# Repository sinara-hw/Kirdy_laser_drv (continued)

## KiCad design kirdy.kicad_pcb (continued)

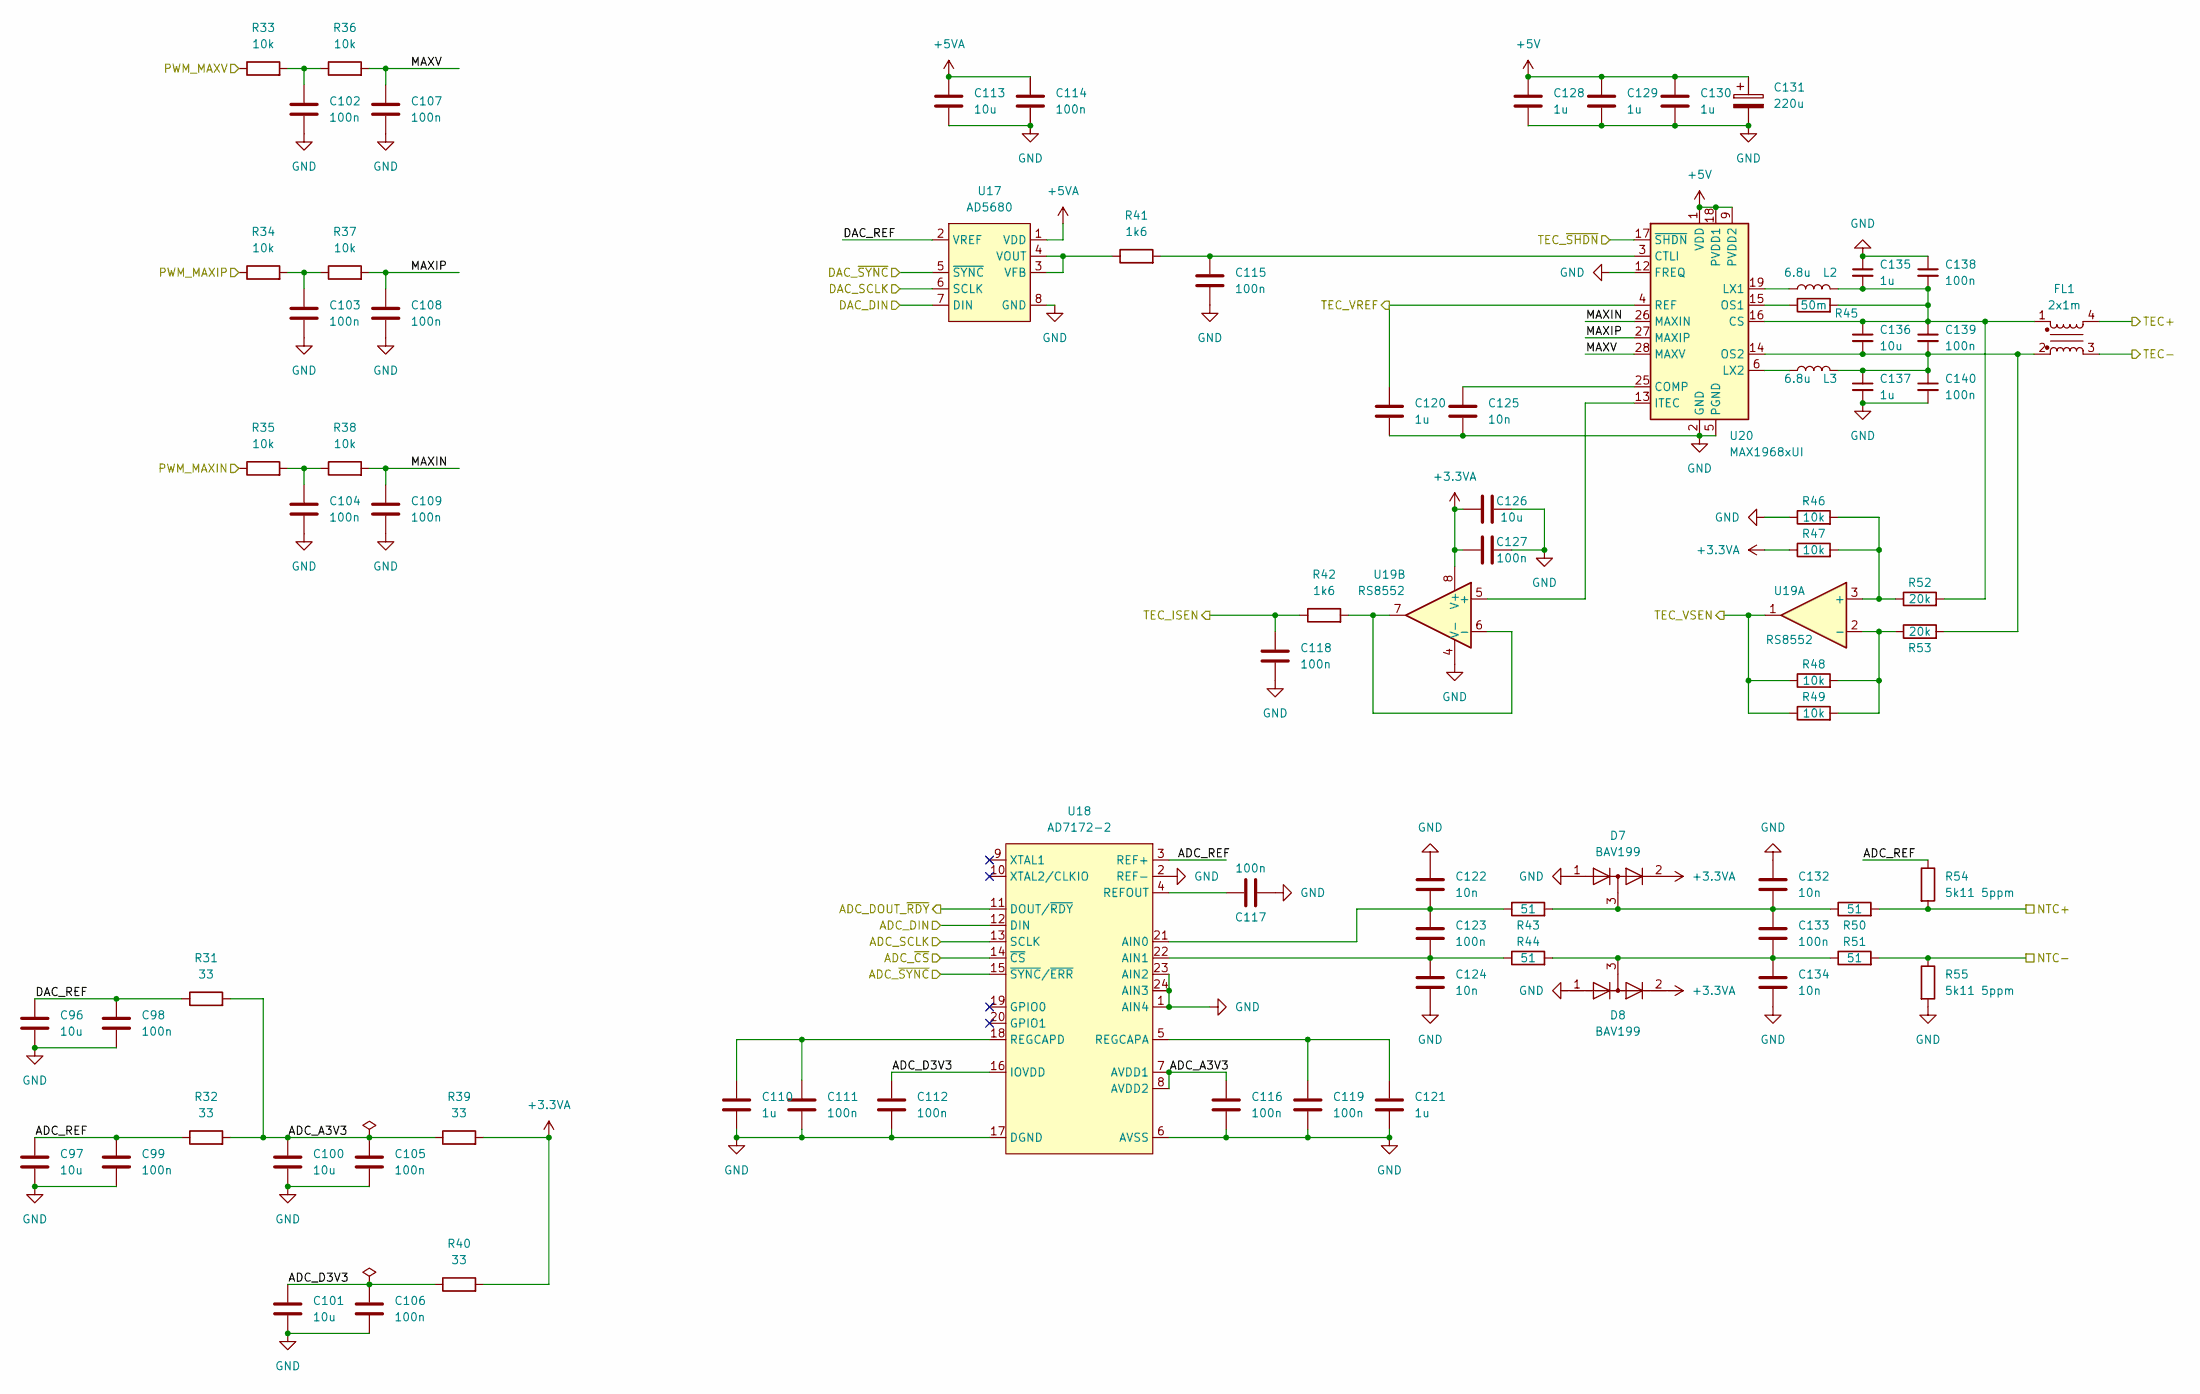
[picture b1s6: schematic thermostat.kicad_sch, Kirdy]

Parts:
C96, C97, C100, C101, C113, C126, C136: 10u; C_0805_2012Metric; MFR_PN CL21B106KOQNNNG
C98, C99, C102, C103, C104, C105, C106, C107, C108, C109, C111, C112, C114, C115, C116, C117, C118, C119, C123, C127, C133, C138, C139, C140: 100n; C_0603_1608Metric; MFR_PN CL10B104KB8NNWC
C110, C120, C121, C128, C129, C130, C135, C137: 1u; C_0603_1608Metric; MFR_PN CL10B105KA8NNNC
C122, C124, C125, C132, C134: 10n; C_0603_1608Metric; MFR_PN 0603B103K500CT
C131: 220u; CP_EIA-7343-15_Kemet-W; MFR_PN T491D227K016AT
D7, D8: BAV199; SOT-23; MFR_PN BAV199W-7
FL1: 2x1m; L_CommonModeChoke_Wuerth_WE-SL5; MFR_PN 744273501
L2, L3: 6.8u; L_Wuerth_MAPI-4030; MFR_PN 74438357068
R31, R32, R39, R40: 33; R_0603_1608Metric; MFR_PN RC0603FR-0733RL
R33, R34, R35, R36, R37, R38, R46, R47, R48, R49: 10k; R_0603_1608Metric; MFR_PN RNCP0603FTD10K0
R41, R42: 1k6; R_0603_1608Metric; MFR_PN RT0603FRE071K6L
R43, R44, R50, R51: 51; R_0603_1608Metric; MFR_PN ESR03EZPF51R0
R45: 50m; R_2010_5025Metric; MFR_PN WSL2010R5000FEA18
R52, R53: 20k; R_0603_1608Metric; MFR_PN RMCF0603FT20K0
R54, R55: 5k11 5ppm; R_0603_1608Metric; MFR_PN RN73H1JTTD5111A05
U17: AD5680; SOT-23-8; MFR_PN AD5680BRJZ
U18: AD7172-2; TSSOP-24_4.4x7.8mm_P0.65mm; MFR_PN AD7172-2BRUZ
U19: RS8552; SOIC-8_3.9x4.9mm_P1.27mm; MFR_PN RS8552XK
U20: MAX1968xUI; HTSSOP-28-1EP_4.4x9.7mm_P0.65mm_EP2.85x5.4mm; MFR_PN MAX1968EUI+

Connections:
+3.3VA: C126.1, C127.1, D7.2 (A), D8.2 (A), R39.2, R40.2, R47.1, U19.8 (V+); also elsewhere on the board
+5V: C128.1, C129.1, C130.1, C131.1, U20.1 (VDD), U20.9 (PVDD2), U20.11 (PVDD2), U20.18 (PVDD1), U20.20 (PVDD1); also elsewhere on the board
+5VA: C113.1, C114.1, U17.1 (VDD); also elsewhere on the board
/MCU/PWM_MAXIN: R35.1; also elsewhere on the board
/MCU/PWM_MAXIP: R34.1; also elsewhere on the board
/MCU/PWM_MAXV: R33.1; also elsewhere on the board
/MCU/TADC_CLK: U18.13 (SCLK); also elsewhere on the board
/MCU/TADC_CS: U18.12 (DIN); also elsewhere on the board
/MCU/TADC_MISO: U18.14 (~CS); also elsewhere on the board
/MCU/TADC_MOSI: U18.11 (DOUT/~RDY); also elsewhere on the board
/MCU/TADC_SYNC: U18.15 (~SYNC/~ERR); also elsewhere on the board
/MCU/TDAC_CLK: U17.6 (SCLK); also elsewhere on the board
/MCU/TDAC_MOSI: U17.7 (DIN); also elsewhere on the board
/MCU/TDAC_SYNC: U17.5 (~SYNC); also elsewhere on the board
/MCU/TEC_ISEN: C118.1, R42.1; also elsewhere on the board
/MCU/TEC_SHDN: U20.17 (~SHDN); also elsewhere on the board
/MCU/TEC_VREF: C120.1, U20.4 (REF); also elsewhere on the board
/MCU/TEC_VSEN: R48.1, R49.1, U19.1; also elsewhere on the board
/thermostat/ADC_A3V3: C100.1, C105.1, C116.1, R31.2, R32.2, R39.1, U18.7 (AVDD1), U18.8 (AVDD2)
/thermostat/ADC_D3V3: C101.1, C106.1, C112.1, R40.1, U18.16 (IOVDD)
/thermostat/ADC_REF: C97.1, C99.1, R32.1, R54.1, U18.3 (REF+)
/thermostat/DAC_REF: C96.1, C98.1, R31.1, U17.2 (VREF)
/thermostat/MAXIN: C109.1, R38.2, U20.26 (MAXIN)
/thermostat/MAXIP: C108.1, R37.2, U20.27 (MAXIP)
/thermostat/MAXV: C107.1, R36.2, U20.28 (MAXV)
/thermostat/NTC+: R50.2, R54.2; also elsewhere on the board
/thermostat/NTC-: R51.2, R55.1; also elsewhere on the board
/thermostat/TEC+: FL1.4; also elsewhere on the board
/thermostat/TEC-: FL1.3; also elsewhere on the board
GND: C96.2, C97.2, C98.2, C99.2, C100.2, C101.2, C102.2, C103.2, C104.2, C105.2, C106.2, C107.2, C108.2, C109.2, C110.2, C111.2, C112.2, C113.2, C114.2, C115.2, C116.2, C117.2, C118.2, C119.2, C120.2, C121.2, C122.1, C124.2, C125.2, C126.2, C127.2, C128.2, C129.2, C130.2, C131.2, C132.1, C134.2, C135.1, C137.2, C138.1, C140.2, D7.1 (K), D8.1 (K), R46.1, R55.2, U17.8 (GND), U18.1 (AIN4), U18.2 (REF-), U18.6 (AVSS), U18.17 (DGND), U18.23 (AIN2), U18.24 (AIN3), U19.4 (V-), U20.2 (GND), U20.5 (PGND), U20.7 (PGND), U20.12 (FREQ), U20.22 (PGND), U20.24 (PGND), U20.29 (GND); also elsewhere on the board
unnamed: C102.1, R33.2, R36.1
unnamed: C103.1, R34.2, R37.1
unnamed: C104.1, R35.2, R38.1
unnamed: C110.1, C111.1, U18.18 (REGCAPD)
unnamed: C115.1, R41.2, U20.3 (CTLI)
unnamed: C117.1, U18.4 (REFOUT)
unnamed: C119.1, C121.1, U18.5 (REGCAPA)
unnamed: C122.2, C123.1, R43.1, U18.21 (AIN0)
unnamed: C123.2, C124.1, R44.1, U18.22 (AIN1)
unnamed: C125.1, U20.25 (COMP)
unnamed: C132.2, C133.1, D7.3 (K), R43.2, R50.1
unnamed: C133.2, C134.1, D8.3 (K), R44.2, R51.1
unnamed: C135.2, C136.1, C138.2, C139.1, FL1.1, L2.2, R45.2, R52.2, U20.16 (CS)
unnamed: C136.2, C137.1, C139.2, C140.1, FL1.2, L3.2, R53.2, U20.14 (OS2)
unnamed: L2.1, U20.19 (LX1), U20.21 (LX1), U20.23 (LX1)
unnamed: L3.1, U20.6 (LX2), U20.8 (LX2), U20.10 (LX2)
unnamed: R41.1, U17.3 (VFB), U17.4 (VOUT)
unnamed: R42.2, U19.6 (-), U19.7
unnamed: R45.1, U20.15 (OS1)
unnamed: R46.2, R47.2, R52.1, U19.3 (+)
unnamed: R48.2, R49.2, R53.1, U19.2 (-)
unnamed: U19.5 (+), U20.13 (ITEC)

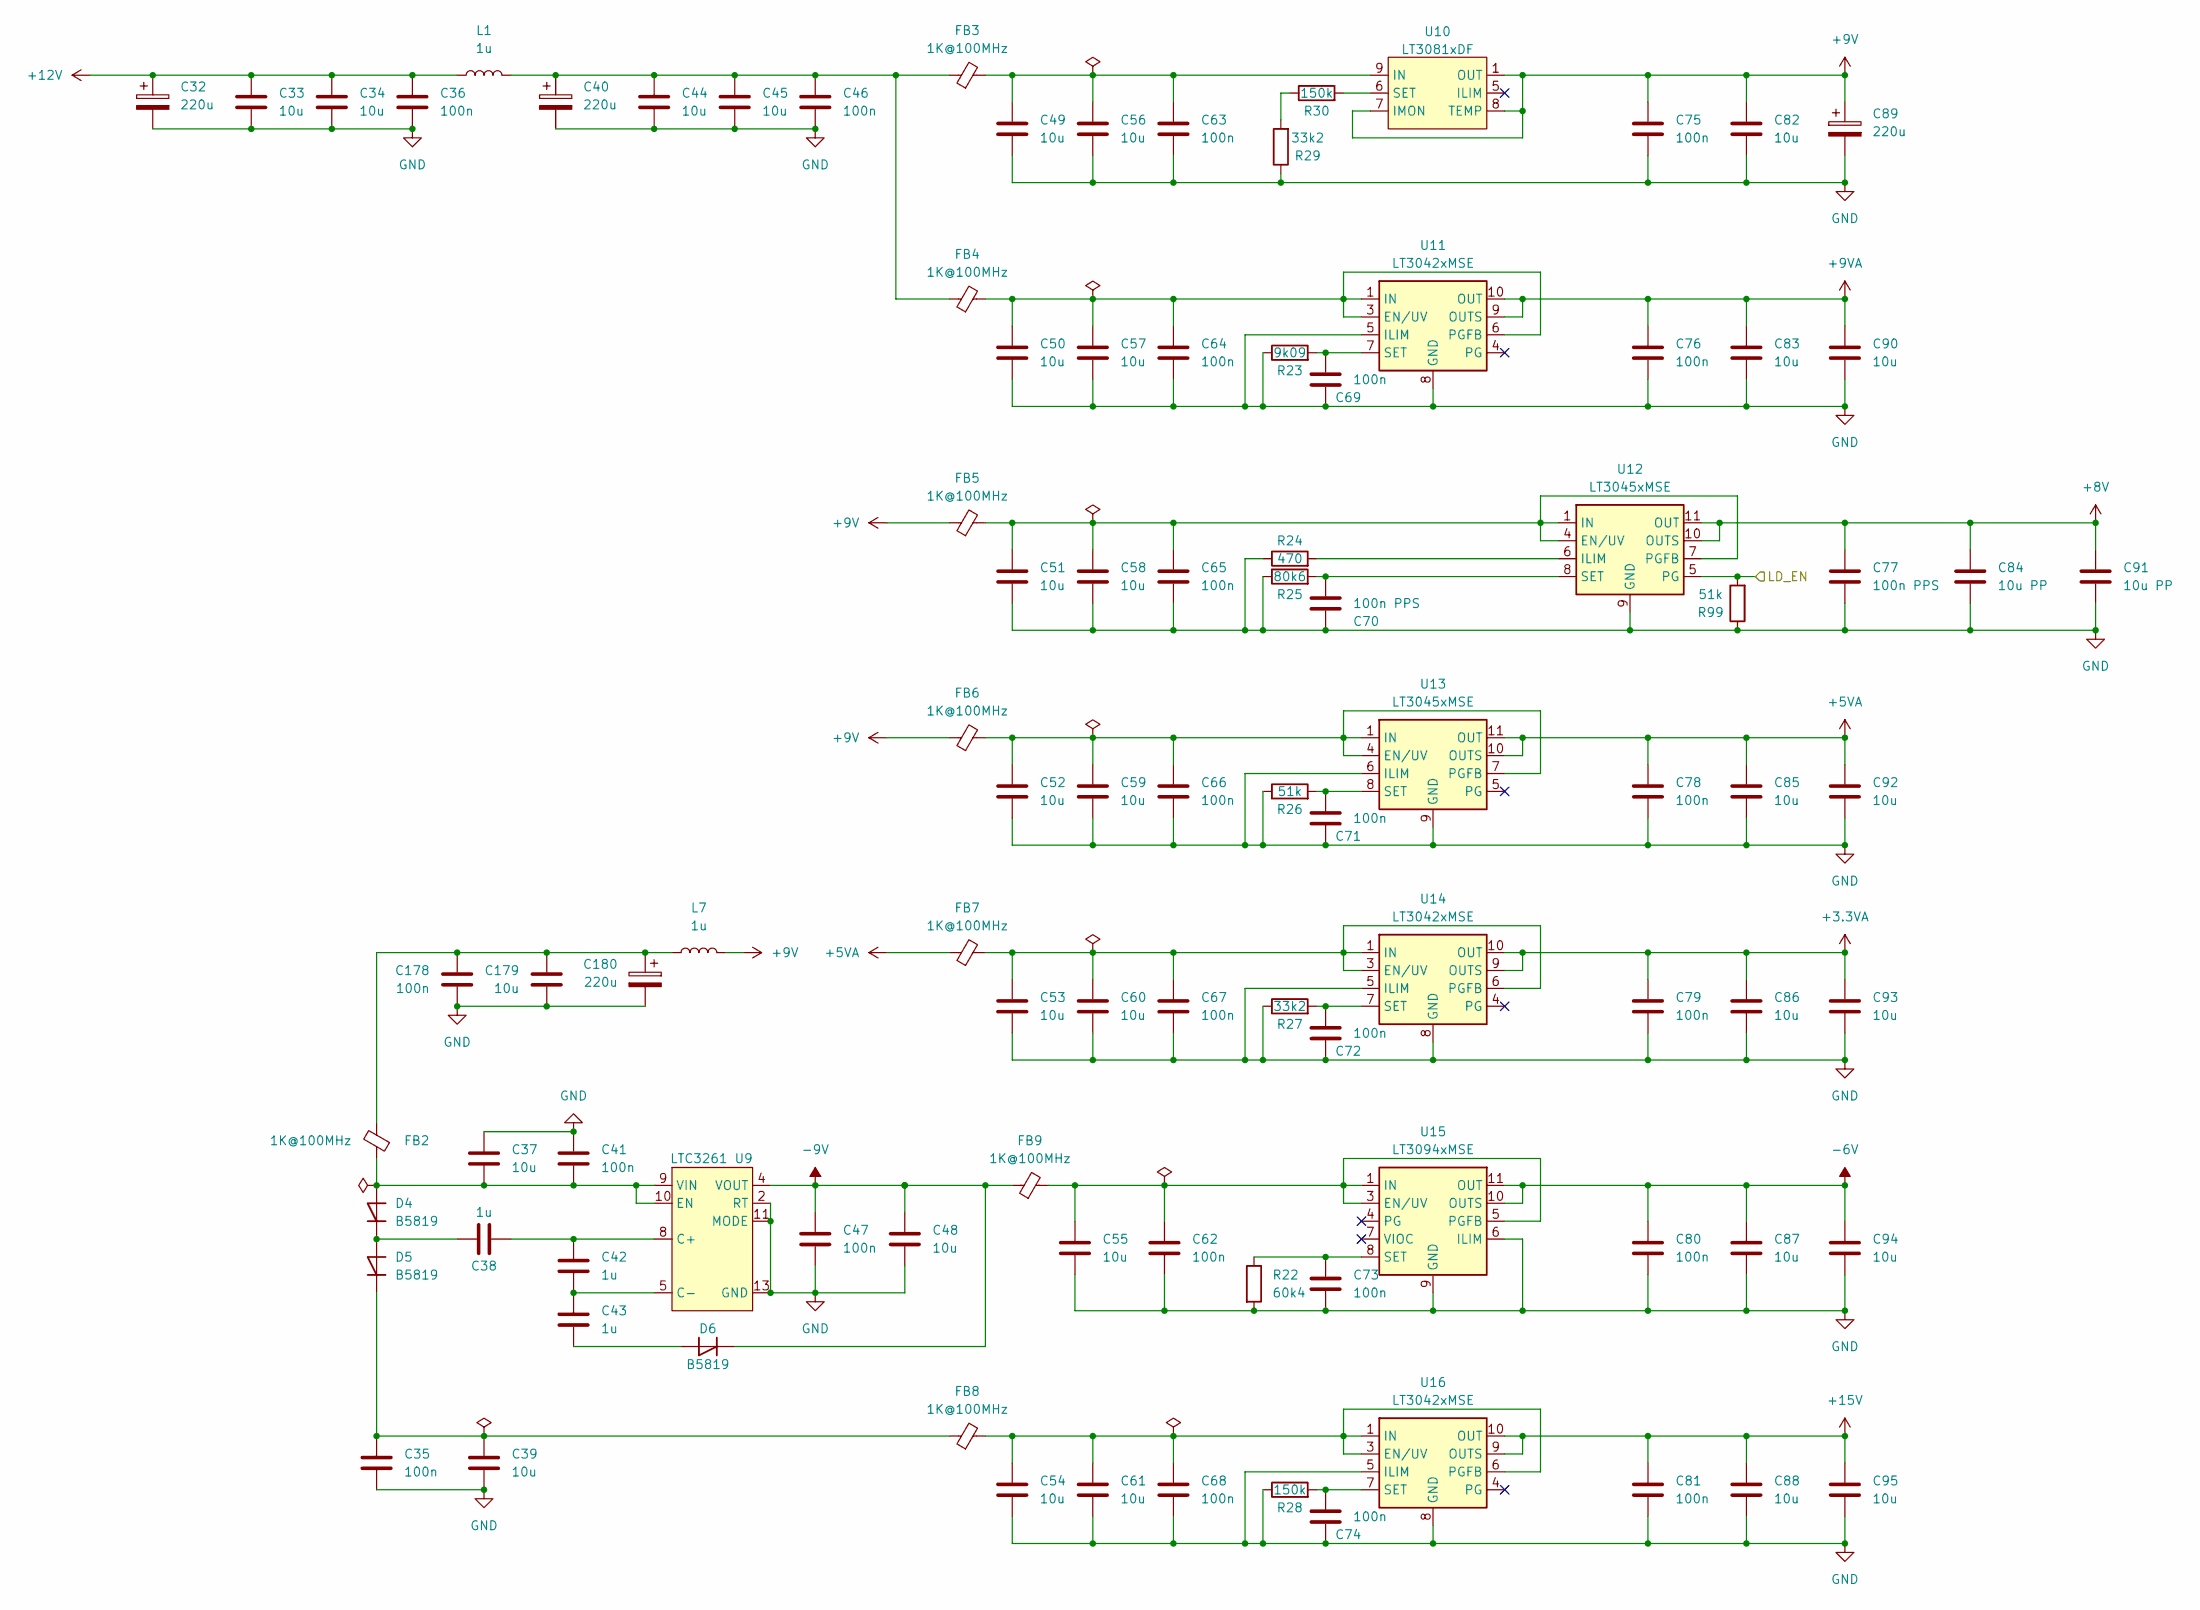
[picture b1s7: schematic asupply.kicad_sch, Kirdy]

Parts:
C32, C40, C89, C180: 220u; CP_EIA-7343-15_Kemet-W; MFR_PN T491D227K016AT
C33, C34, C37, C39, C44, C45, C48, C49, C50, C51, C52, C53, C54, C55, C56, C57, C58, C59, C60, C61, C82, C83, C85, C86, C87, C88, C90, C92, C93, C94, C95, C179: 10u; C_0805_2012Metric; MFR_PN CL21B106KOQNNNG
C35, C36, C41, C46, C47, C62, C63, C64, C65, C66, C67, C68, C69, C71, C72, C73, C74, C75, C76, C78, C79, C80, C81, C178: 100n; C_0603_1608Metric; MFR_PN CL10B104KB8NNWC
C38, C42, C43: 1u; C_0603_1608Metric; MFR_PN CL10B105KA8NNNC
C70, C77: 100n PPS; C_1210_3225Metric; MFR_PN ECH-U1C104JX5
C84, C91: 10u PP; C_1812_4532Metric; MFR_PN 16MU106MC44532
D4, D5, D6: B5819; D_SOD-323; MFR_PN B5819WS-TP
FB2, FB3, FB4, FB5, FB6, FB7, FB8, FB9: 1K@100MHz; L_1210_3225Metric; MFR_PN FBMH3225HM102NT
L1, L7: 1u; L_1008_2520Metric; MFR_PN DFE252012F-1R0M=P2
R22: 60k4; R_0603_1608Metric; MFR_PN RT0603FRE0760K4L
R23: 9k09; R_0603_1608Metric; MFR_PN CR0603-FX-9091ELF
R24: 470; R_0603_1608Metric; MFR_PN WR06X4700FTL
R25: 80k6; R_0603_1608Metric; MFR_PN RC0603FR-0780K6L
R26, R99: 51k; R_0603_1608Metric; MFR_PN RMCF0603FT51K0
R27, R29: 33k2; R_0603_1608Metric; MFR_PN CR0603-FX-3322ELF
R28, R30: 150k; R_0603_1608Metric; MFR_PN CRGCQ0603F150K
U9: LTC3261; MSOP-12-1EP_3x4mm_P0.65mm_EP1.65x2.85mm; MFR_PN LTC3261IMSE#TRPBF
U10: LT3081xDF; DFN-12-1EP_4x4mm_P0.5mm_EP2.66x3.38mm; MFR_PN LT3081EDF
U11, U14, U16: LT3042xMSE; MSOP-10-1EP_3x3mm_P0.5mm_EP1.68x1.88mm; MFR_PN LT3042IMSE#PBF
U12, U13: LT3045xMSE; MSOP-12-1EP_3x4mm_P0.65mm_EP1.65x2.85mm; MFR_PN LT3045EMSE-1#PBF
U15: LT3094xMSE; MSOP-12-1EP_3x4mm_P0.65mm_EP1.65x2.85mm; MFR_PN LT3094IMSE#PBF

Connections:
+3.3VA: C79.1, C86.1, C93.1, U14.9 (OUTS), U14.10 (OUT); also elsewhere on the board
+5VA: C78.1, C85.1, C92.1, FB7.1, U13.10 (OUTS), U13.11 (OUT), U13.12 (OUT); also elsewhere on the board
+8V: C77.1, C84.1, C91.1, U12.10 (OUTS), U12.11 (OUT), U12.12 (OUT); also elsewhere on the board
+9V: C75.1, C82.1, C89.1, FB5.1, FB6.1, L7.1, U10.1 (OUT), U10.2 (OUT), U10.3 (OUT), U10.4 (OUT), U10.7 (IMON), U10.8 (TEMP), U10.13 (OUT)
+9VA: C76.1, C83.1, C90.1, U11.9 (OUTS), U11.10 (OUT); also elsewhere on the board
+12V: C32.1, C33.1, C34.1, C36.1, L1.1; also elsewhere on the board
+15V: C81.1, C88.1, C95.1, U16.9 (OUTS), U16.10 (OUT); also elsewhere on the board
-6V: C80.1, C87.1, C94.1, U15.10 (OUTS), U15.11 (OUT), U15.12 (OUT); also elsewhere on the board
-9V: C47.1, C48.1, D6.1 (K), FB9.1, U9.4 (VOUT)
/MCU/LD_EN: R99.2, U12.5 (PG); also elsewhere on the board
GND: C32.2, C33.2, C34.2, C35.2, C36.2, C37.1, C39.2, C40.2, C41.1, C44.2, C45.2, C46.2, C47.2, C48.2, C49.2, C50.2, C51.2, C52.2, C53.2, C54.2, C55.2, C56.2, C57.2, C58.2, C59.2, C60.2, C61.2, C62.2, C63.2, C64.2, C65.2, C66.2, C67.2, C68.2, C69.2, C70.2, C71.2, C72.2, C73.2, C74.2, C75.2, C76.2, C77.2, C78.2, C79.2, C80.2, C81.2, C82.2, C83.2, C84.2, C85.2, C86.2, C87.2, C88.2, C89.2, C90.2, C91.2, C92.2, C93.2, C94.2, C95.2, C178.2, C179.2, C180.2, R22.2, R23.1, R24.1, R25.1, R26.1, R27.1, R28.1, R29.1, R99.1, U9.2 (RT), U9.11 (MODE), U9.13 (GND), U11.5 (ILIM), U11.8 (GND), U11.11 (GND), U12.9 (GND), U12.13 (GND), U13.6 (ILIM), U13.9 (GND), U13.13 (GND), U14.5 (ILIM), U14.8 (GND), U14.11 (GND), U15.6 (ILIM), U15.9 (GND), U16.5 (ILIM), U16.8 (GND), U16.11 (GND); also elsewhere on the board
IN: C49.1, C56.1, C63.1, FB3.2, U10.9 (IN), U10.10 (IN), U10.11 (IN), U10.12 (IN)
unnamed: C35.1, C39.1, D5.1 (K), FB8.1
unnamed: C37.2, C41.2, D4.2 (A), FB2.1, U9.9 (VIN), U9.10 (EN)
unnamed: C38.1, D4.1 (K), D5.2 (A)
unnamed: C38.2, C42.1, U9.8 (C+)
unnamed: C40.1, C44.1, C45.1, C46.1, FB3.1, FB4.1, L1.2
unnamed: C42.2, C43.1, U9.5 (C-)
unnamed: C43.2, D6.2 (A)
unnamed: C50.1, C57.1, C64.1, FB4.2, U11.1 (IN), U11.2 (IN), U11.3 (EN/UV), U11.6 (PGFB)
unnamed: C51.1, C58.1, C65.1, FB5.2, U12.1 (IN), U12.2 (IN), U12.3 (IN), U12.4 (EN/UV), U12.7 (PGFB)
unnamed: C52.1, C59.1, C66.1, FB6.2, U13.1 (IN), U13.2 (IN), U13.3 (IN), U13.4 (EN/UV), U13.7 (PGFB)
unnamed: C53.1, C60.1, C67.1, FB7.2, U14.1 (IN), U14.2 (IN), U14.3 (EN/UV), U14.6 (PGFB)
unnamed: C54.1, C61.1, C68.1, FB8.2, U16.1 (IN), U16.2 (IN), U16.3 (EN/UV), U16.6 (PGFB)
unnamed: C55.1, C62.1, FB9.2, U15.1 (IN), U15.2 (IN), U15.3 (EN/UV), U15.5 (PGFB), U15.13 (IN)
unnamed: C69.1, R23.2, U11.7 (SET)
unnamed: C70.1, R25.2, U12.8 (SET)
unnamed: C71.1, R26.2, U13.8 (SET)
unnamed: C72.1, R27.2, U14.7 (SET)
unnamed: C73.1, R22.1, U15.8 (SET)
unnamed: C74.1, R28.2, U16.7 (SET)
unnamed: C178.1, C179.1, C180.1, FB2.2, L7.2
unnamed: R24.2, U12.6 (ILIM)
unnamed: R29.2, R30.1
unnamed: R30.2, U10.6 (SET)

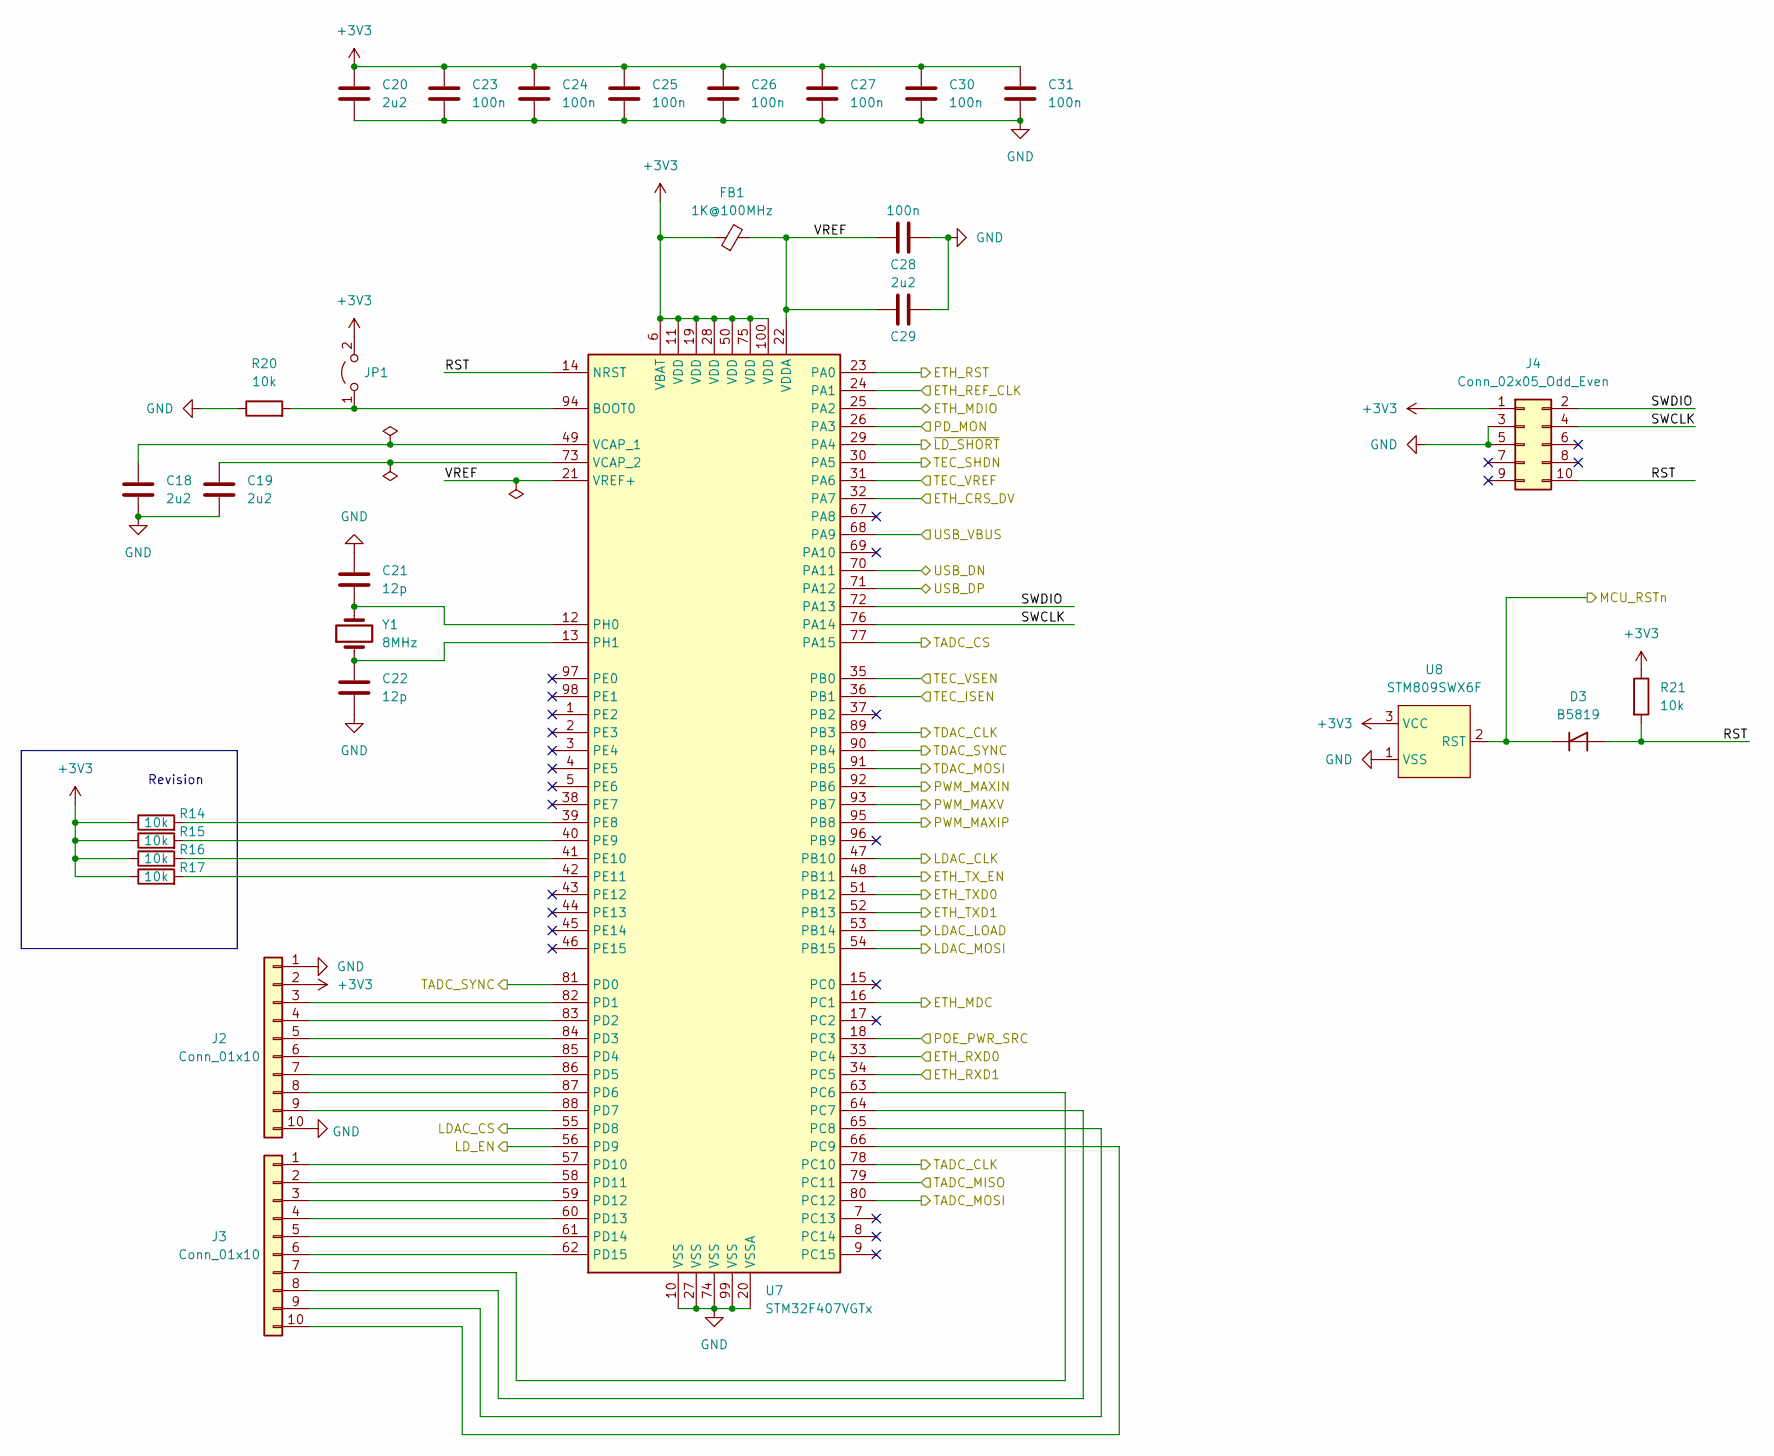
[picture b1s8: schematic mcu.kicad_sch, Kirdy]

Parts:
C18, C19, C20, C29: 2u2; C_0603_1608Metric; MFR_PN CL10B225KP8NNNC
C21, C22: 12p; C_0603_1608Metric; MFR_PN 0603N120J500CT
C23, C24, C25, C26, C27, C28, C30, C31: 100n; C_0603_1608Metric; MFR_PN CL10B104KB8NNWC
D3: B5819; D_SOD-323; MFR_PN B5819WS-TP
FB1: 1K@100MHz; L_1210_3225Metric; MFR_PN FBMH3225HM102NT
J2, J3: Conn_01x10; PinHeader_1x10_P2.54mm_Vertical
J4: Conn_02x05_Odd_Even; PinHeader_2x05_P1.27mm_Vertical_SMD; MFR_PN M50-3600542
JP1: DNP; PinHeader_1x02_P2.54mm_Vertical
R14, R15, R16, R17, R20, R21: 10k; R_0603_1608Metric; MFR_PN RNCP0603FTD10K0
U7: STM32F407VGTx; LQFP-100_14x14mm_P0.5mm; MFR_PN STM32F407VGT6
U8: STM809SWX6F; SOT-23; MFR_PN STM809SWX6F
Y1: 8MHz; Crystal_SMD_5032-2Pin_5.0x3.2mm; MFR_PN ECS-80-12-30Q-DS-TR

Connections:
+3V3: C20.1, C23.1, C24.1, C25.1, C26.1, C27.1, C30.1, C31.1, FB1.1, J2.2, J4.1, JP1.2 (B), R14.1, R15.1, R16.1, R17.1, R21.1, U7.6 (VBAT), U7.11 (VDD), U7.19 (VDD), U7.28 (VDD), U7.50 (VDD), U7.75 (VDD), U7.100 (VDD), U8.3 (VCC); also elsewhere on the board
/Ehternet/PHY_NRST: U7.23 (PA0); also elsewhere on the board
/Ehternet/RMII_CRS_DV: U7.32 (PA7); also elsewhere on the board
/Ehternet/RMII_MDC: U7.16 (PC1); also elsewhere on the board
/Ehternet/RMII_MDIO: U7.25 (PA2); also elsewhere on the board
/Ehternet/RMII_REF_CLK: U7.24 (PA1); also elsewhere on the board
/Ehternet/RMII_RXD0: U7.33 (PC4); also elsewhere on the board
/Ehternet/RMII_RXD1: U7.34 (PC5); also elsewhere on the board
/Ehternet/RMII_TXD0: U7.51 (PB12); also elsewhere on the board
/Ehternet/RMII_TXD1: U7.52 (PB13); also elsewhere on the board
/Ehternet/RMII_TX_EN: U7.48 (PB11); also elsewhere on the board
/MCU/LDAC_CLK: U7.47 (PB10); also elsewhere on the board
/MCU/LDAC_CS: U7.55 (PD8); also elsewhere on the board
/MCU/LDAC_LOAD: U7.53 (PB14); also elsewhere on the board
/MCU/LDAC_MOSI: U7.54 (PB15); also elsewhere on the board
/MCU/LD_EN: U7.56 (PD9); also elsewhere on the board
/MCU/MCU_RSTn: D3.1 (K), U8.2 (RST); also elsewhere on the board
/MCU/PD_MON: U7.26 (PA3); also elsewhere on the board
/MCU/POE_PWR_SRC: U7.18 (PC3); also elsewhere on the board
/MCU/PWM_MAXIN: U7.92 (PB6); also elsewhere on the board
/MCU/PWM_MAXIP: U7.95 (PB8); also elsewhere on the board
/MCU/PWM_MAXV: U7.93 (PB7); also elsewhere on the board
/MCU/RST: D3.2 (A), J4.10, R21.2, U7.14 (NRST)
/MCU/SWCLK: J4.4, U7.76 (PA14)
/MCU/SWDIO: J4.2, U7.72 (PA13)
/MCU/TADC_CLK: U7.78 (PC10); also elsewhere on the board
/MCU/TADC_CS: U7.77 (PA15); also elsewhere on the board
/MCU/TADC_MISO: U7.79 (PC11); also elsewhere on the board
/MCU/TADC_MOSI: U7.80 (PC12); also elsewhere on the board
/MCU/TADC_SYNC: U7.81 (PD0); also elsewhere on the board
/MCU/TDAC_CLK: U7.89 (PB3); also elsewhere on the board
/MCU/TDAC_MOSI: U7.91 (PB5); also elsewhere on the board
/MCU/TDAC_SYNC: U7.90 (PB4); also elsewhere on the board
/MCU/TEC_ISEN: U7.36 (PB1); also elsewhere on the board
/MCU/TEC_SHDN: U7.30 (PA5); also elsewhere on the board
/MCU/TEC_VREF: U7.31 (PA6); also elsewhere on the board
/MCU/TEC_VSEN: U7.35 (PB0); also elsewhere on the board
/MCU/USB_DN: U7.70 (PA11); also elsewhere on the board
/MCU/USB_DP: U7.71 (PA12); also elsewhere on the board
/MCU/USB_VBUS: U7.68 (PA9); also elsewhere on the board
/MCU/VREF: C28.1, C29.1, FB1.2, U7.21 (VREF+), U7.22 (VDDA)
/MCU/~LD_SHORT: U7.29 (PA4); also elsewhere on the board
GND: C18.2, C19.2, C20.2, C21.1, C22.2, C23.2, C24.2, C25.2, C26.2, C27.2, C28.2, C29.2, C30.2, C31.2, J2.1, J2.10, J4.3, J4.5, R20.1, U7.10 (VSS), U7.20 (VSSA), U7.27 (VSS), U7.74 (VSS), U7.99 (VSS), U8.1 (VSS); also elsewhere on the board
unnamed: C18.1, U7.49 (VCAP_1)
unnamed: C19.1, U7.73 (VCAP_2)
unnamed: C21.2, U7.12 (PH0), Y1.2
unnamed: C22.1, U7.13 (PH1), Y1.1
unnamed: J2.3, U7.82 (PD1)
unnamed: J2.4, U7.83 (PD2)
unnamed: J2.5, U7.84 (PD3)
unnamed: J2.6, U7.85 (PD4)
unnamed: J2.7, U7.86 (PD5)
unnamed: J2.8, U7.87 (PD6)
unnamed: J2.9, U7.88 (PD7)
unnamed: J3.1, U7.57 (PD10)
unnamed: J3.2, U7.58 (PD11)
unnamed: J3.3, U7.59 (PD12)
unnamed: J3.4, U7.60 (PD13)
unnamed: J3.5, U7.61 (PD14)
unnamed: J3.6, U7.62 (PD15)
unnamed: J3.7, U7.63 (PC6)
unnamed: J3.8, U7.64 (PC7)
unnamed: J3.9, U7.65 (PC8)
unnamed: J3.10, U7.66 (PC9)
unnamed: JP1.1 (A), R20.2, U7.94 (BOOT0)
unnamed: R14.2, U7.39 (PE8)
unnamed: R15.2, U7.40 (PE9)
unnamed: R16.2, U7.41 (PE10)
unnamed: R17.2, U7.42 (PE11)

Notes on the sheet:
Revision

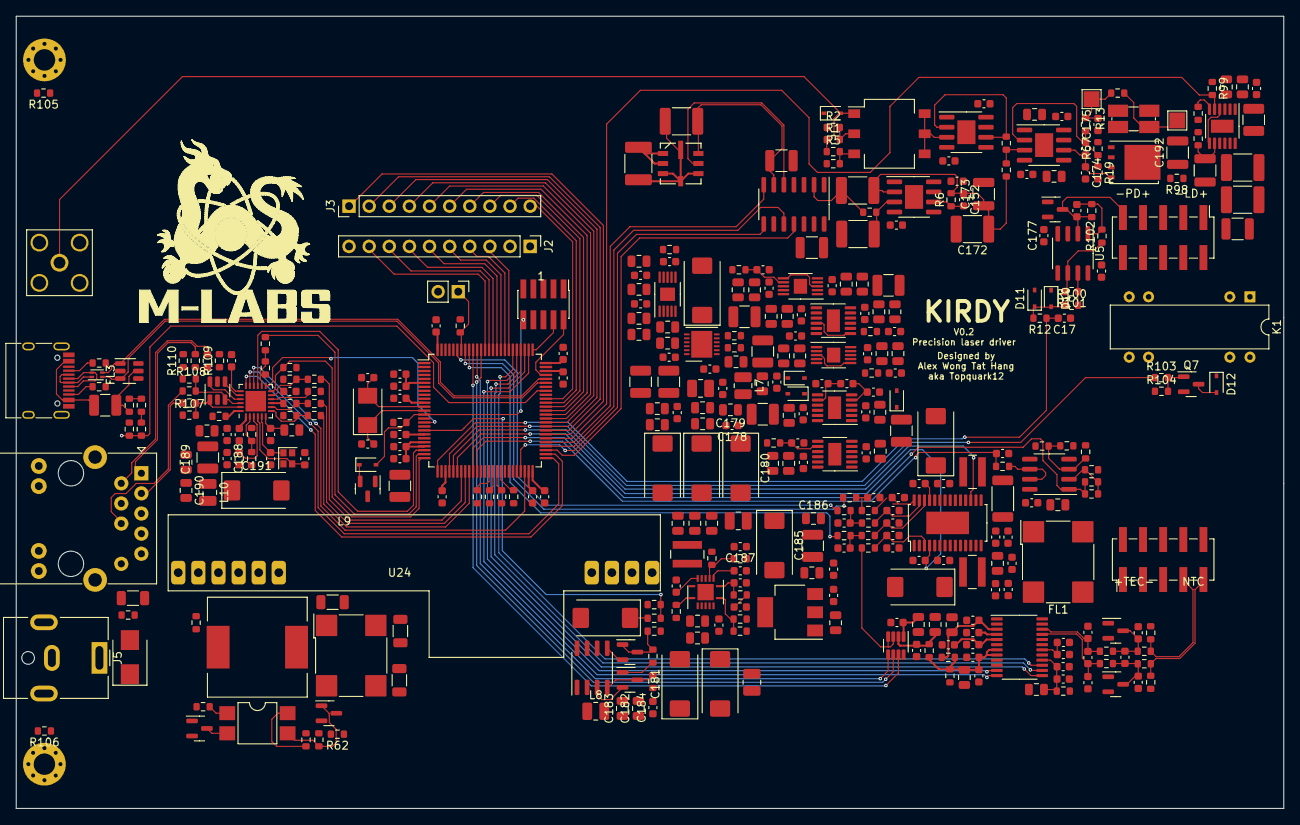
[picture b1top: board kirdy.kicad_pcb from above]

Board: 4 copper layers, 160.0 x 100.0 mm, 390 parts (0 on the bottom side), 224 nets.

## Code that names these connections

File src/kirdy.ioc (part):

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Mcu.Name=STM32F407V(E-G)Tx
Mcu.Package=LQFP100
Mcu.UserName=STM32F407VGTx
PA0-WKUP.GPIOParameters=GPIO_Label
PA0-WKUP.GPIO_Label=ETH_RST
PA0-WKUP.Signal=GPIO_Output
PA1.Mode=RMII
PA1.Signal=ETH_REF_CLK
PA11.Mode=Device_Only
PA11.Signal=USB_OTG_FS_DM
PA12.Mode=Device_Only
PA12.Signal=USB_OTG_FS_DP
PA13.Mode=Serial_Wire
PA13.Signal=SYS_JTMS-SWDIO
PA14.Mode=Serial_Wire
PA14.Signal=SYS_JTCK-SWCLK
PA15.GPIOParameters=GPIO_Label
PA15.GPIO_Label=TADC_CS
PA15.Mode=NSS_Signal_Hard_Output
PA15.Signal=SPI3_NSS
PA2.Mode=RMII
PA2.Signal=ETH_MDIO
PA3.GPIOParameters=GPIO_Label
PA3.GPIO_Label=PD_MON
PA3.Signal=ADCx_IN3
PA4.GPIOParameters=GPIO_Label
PA4.GPIO_Label=PD_BIAS
PA4.Signal=COMP_DAC1_group
PA5.GPIOParameters=GPIO_Label
PA5.GPIO_Label=TEC_SHDN
PA5.Signal=GPIO_Output
PA6.GPIOParameters=GPIO_Label
PA6.GPIO_Label=TEC_VREF
PA6.Signal=ADCx_IN6
PA7.Mode=RMII
PA7.Signal=ETH_CRS_DV
PA8.Mode=I2C
PA8.Signal=I2C3_SCL
PA9.Mode=Activate_VBUS
PA9.Signal=USB_OTG_FS_VBUS
PB0.GPIOParameters=GPIO_Label
PB0.GPIO_Label=TEC_ISEN
PB0.Signal=ADCx_IN8
PB1.GPIOParameters=GPIO_Label
PB1.GPIO_Label=TEC_VSEN
PB1.Signal=ADCx_IN9
PB10.GPIOParameters=GPIO_Label
PB10.GPIO_Label=LDAC_CLK
PB10.Mode=TX_Only_Simplex_Unidirect_Master
PB10.Signal=SPI2_SCK
PB11.Mode=RMII
PB11.Signal=ETH_TX_EN
PB12.Mode=RMII
PB12.Signal=ETH_TXD0
PB13.Mode=RMII
PB13.Signal=ETH_TXD1
PB14.GPIOParameters=GPIO_Label
PB14.GPIO_Label=LDAC_LOAD
PB14.Signal=GPIO_Output
PB15.GPIOParameters=GPIO_Label
PB15.GPIO_Label=LDAC_MOSI
PB15.Mode=TX_Only_Simplex_Unidirect_Master
PB15.Signal=SPI2_MOSI
PB3.GPIOParameters=GPIO_Label
PB3.GPIO_Label=TDAC_CLK
PB3.Mode=TX_Only_Simplex_Unidirect_Master
PB3.Signal=SPI1_SCK
PB4.GPIOParameters=GPIO_Label
PB4.GPIO_Label=TDAC_SYNC
PB4.Signal=GPIO_Output
PB5.GPIOParameters=GPIO_Label
PB5.GPIO_Label=TDAC_MOSI
PB5.Mode=TX_Only_Simplex_Unidirect_Master
PB5.Signal=SPI1_MOSI
PB6.GPIOParameters=GPIO_Label
PB6.GPIO_Label=PWM_MAXIN
PB6.Signal=S_TIM4_CH1
PB7.GPIOParameters=GPIO_Label
PB7.GPIO_Label=PWM_MAXV
PB7.Signal=S_TIM4_CH2
PB8.GPIOParameters=GPIO_Label
PB8.GPIO_Label=PWM_MAXIP
PB8.Signal=S_TIM4_CH3
PC1.Mode=RMII
PC1.Signal=ETH_MDC
PC10.GPIOParameters=GPIO_Label
PC10.GPIO_Label=TADC_CLK
PC10.Mode=Full_Duplex_Master
PC10.Signal=SPI3_SCK
PC11.GPIOParameters=GPIO_Label
PC11.GPIO_Label=TADC_MISO
PC11.Mode=Full_Duplex_Master
PC11.Signal=SPI3_MISO
PC12.GPIOParameters=GPIO_Label
PC12.GPIO_Label=TADC_MOSI
PC12.Mode=Full_Duplex_Master
PC12.Signal=SPI3_MOSI
PC2.GPIOParameters=GPIO_Label
PC2.GPIO_Label=AT_EVENT
PC2.Signal=GPIO_Input
PC3.GPIOParameters=GPIO_Label
PC3.GPIO_Label=POE_PWR_SRC
PC3.Signal=GPIO_Input
PC4.Mode=RMII
PC4.Signal=ETH_RXD0
PC5.Mode=RMII
PC5.Signal=ETH_RXD1
PC9.Mode=I2C
PC9.Signal=I2C3_SDA
PD0.GPIOParameters=GPIO_Label
PD0.GPIO_Label=TADC_SYNC
PD0.Signal=GPIO_Output
PD8.GPIOParameters=GPIO_Label
PD8.GPIO_Label=LDAC_CS
PD8.Signal=GPIO_Output
PD9.GPIOParameters=GPIO_Label
PD9.GPIO_Label=LD_EN
PD9.Signal=GPIO_Output
PE10.GPIOParameters=GPIO_Label
PE10.GPIO_Label=REV2
PE10.Signal=GPIO_Input
PE11.GPIOParameters=GPIO_Label
PE11.GPIO_Label=REV3
PE11.Signal=GPIO_Input
PE12.GPIOParameters=GPIO_Label
PE12.GPIO_Label=REV4
PE12.Signal=GPIO_Input
PE13.GPIOParameters=GPIO_Label
PE13.GPIO_Label=REV5
PE13.Signal=GPIO_Input
PE8.GPIOParameters=GPIO_Label
PE8.GPIO_Label=REV0
PE8.Signal=GPIO_Input
PE9.GPIOParameters=GPIO_Label
PE9.GPIO_Label=REV1
PE9.Signal=GPIO_Input
PH0-OSC_IN.Mode=HSE-External-Oscillator
PH0-OSC_IN.Signal=RCC_OSC_IN
PH1-OSC_OUT.Mode=HSE-External-Oscillator
PH1-OSC_OUT.Signal=RCC_OSC_OUT
RCC.HSE_VALUE=25000000
RCC.SYSCLKFreq_VALUE=168000000
RCC.SYSCLKSource=RCC_SYSCLKSOURCE_PLLCLK
board=custom
